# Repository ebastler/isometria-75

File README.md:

# isometria<sup>75</sup>

The first prototype is sitting on my desk and works perfectly - clearance for weights and battery is currently wrong, so the intended battery will not fit in the case.

----
 
 The name isometria<sup>75</sup> has it's origin in the greek noun ἰσομετρία (in latin letters: isometria), meaning "equality of measure" [[1]](http://perseus.uchicago.edu/cgi-bin/philologic/getobject.pl?c.35:6:59.LSJ). This word ended up being included in various languages, among them english (isometric), with the same meaning. I chose it for two reasons - because this keyboard is only available in an ISO layout (sorry ANSI users - for once it is ne ANSI avail), but also, because I paid attention to only use u/4 spaces throughout my board. You will have a hard time finding any distance on it that's not a multiple of 4.75 mm.

|||
|:----------------------------------------:|:----------------------------------------:|
|||
|||

 ## Features
 * CNC'd top shell with integrated 3 mm plate (obviously, with cutouts for switch retention and PCB mount stabs)
 * 6.8° typing angle
 * The PCB is equipped to fit 82 cherry MX-style switches
 * One 3 mm LED per switch (monochrome, dimmable only as one group)
 * 17 SK6812 Mini can be soldered to the bottom of the board for underglow
 * Fits either a battery-management or a simple USB-C daughterboard ([Repo link](https://github.com/ebastler/unified-usb-pcb))
 * A rotary encoder sits in the top right corner and the push-button is wired to the controller (Row 0 Column 15)
 * The USB-C connector is placed on a small PCB on it's own, which can be replaced by a battery management board
 * Sense wires to measure the input voltage and to check if the battery is currently being charged
 * A STM32F072CBT6 controller with native crystal-less USB and a lot of IO for various things
 * An SPI interface is wired to a second connector, allowing for a SPI Bluetooth LE board to be added
 * One leftover GPIO is available on a header - if you want to add something yourself

## Design
The PCB uses a key spacing of 19 mm (instead of the default 19.05), and all delimiters between key-blocks, or keys and the border of the case are 4.75 or 9.5 mm wide. This allows for a pleasantly homogenous design, which earned the keyboard it's name. Sadly, this layout requires a 1.5u right shift, which very few sets include. 

The bottom shell breaks the minimalist design of the top shell a little, with "stepped" faces. While the design originated from the need to make it easily millable on a 3 axis CNC, I appreciate the fact that it makes the board visually a bit more interesting.

## Geekhack project thread
https://geekhack.org/index.php?topic=106060.msg2896354

## FAQ:
 * Where can I buy this?

   I'm afraid there will not be any groupbuy nor will it be stocked at some reseller - All files are open source though, feel free to order a batch of PCBs and a case yourself - or improve it!

 * When will there be an ANSI version?

   Even though I planned not to do ANSI, I actually went with multi-layout for v2! Stay tuned!

 * Why did you clone the Evolv/Satisfaction?
 
   I made my own design choices, and designed everything from scratch - however the evolv heavily influenced my design. I fell in love with it the first time I saw it, but it had a few things I dislike. So I decided to mostly adopt it's layout with some changes, and design a case which follows my design ideals - ending up with a (visually) very similar top enclosure - The standalone-features of the evolv are it's premium materials, construction and generative design, and I did not include either.

For any other questions, or problems with my board (if you decided to build one yourself) - feel free to contact me. I'm idling around and occasionally check my PMs on freenode (ebastler), am active on reddit (the_ebastler) and on discord (ebastler#8966).

## Big thanks to:
 - ai03 for both his [great tutorial](https://wiki.ai03.me/books/pcb-design/chapter/pcb-designer-guide) as well as his various footprints I used in my design - I don't know if I had been able to design this without his help.
 - The awesome people on grabcad for the [MX switch](https://grabcad.com/library/cherry-mx-switches-mx-1), [Cherry Stab](https://grabcad.com/library/cherry-mx-stabilizer-mx-1) and [pushbutton](https://grabcad.com/library/5mm-button-switch-1) models, [JST SH models](https://grabcad.com/library/jst-sh-smd-connectors-1/details?folder_id=3903823) and [WS2812 Mini models](https://grabcad.com/library/smd-ws2812b-led-1) which made my design a whole lot easier, and my renders prettier.
  - People on the MechKeys and Mechanische Tastaturen Deutschland discord servers who tirelessly answered my questions - from the noobiest to the most complicated ones.
  - [Propagandalf1](https://github.com/Propagandalf1) for all the advise, criticism and ideas for improvement
  - Pseudoephedrin and Lux for checking my PCB layouts for errors
  - Hendrik for milling my proto

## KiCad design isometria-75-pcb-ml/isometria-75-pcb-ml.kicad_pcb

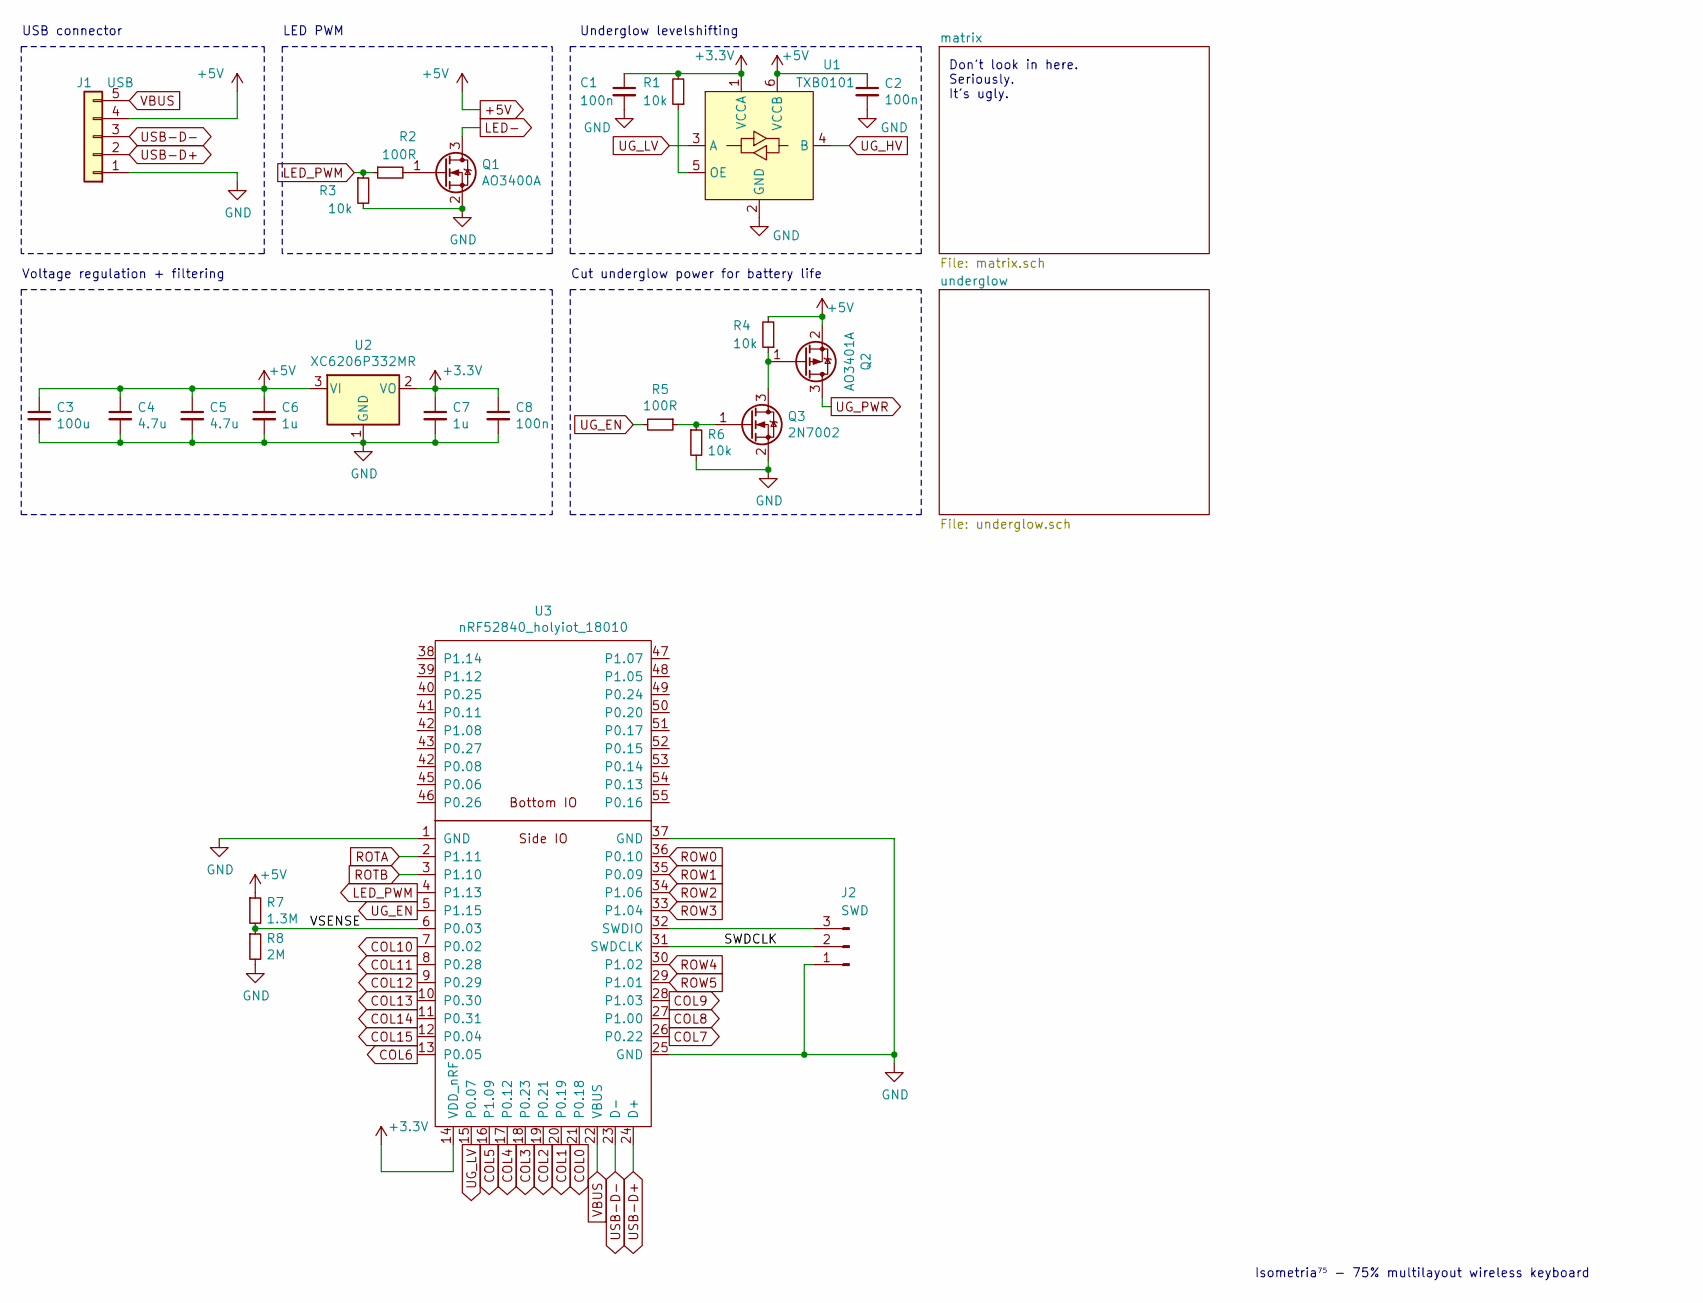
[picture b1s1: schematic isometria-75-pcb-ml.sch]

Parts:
C1, C2, C8: 100n; C_0603_1608Metric_Pad1.05x0.95mm_HandSolder; LCSC C386152
C3: 100u; CP_EIA-3528-21_Kemet-B; LCSC C16133
C4, C5: 4.7u; C_0603_1608Metric_Pad1.05x0.95mm_HandSolder; LCSC C1705
C6, C7: 1u; C_0603_1608Metric_Pad1.05x0.95mm_HandSolder; LCSC C15849
J1: USB; JST_SH_SM05B-SRSS-TB_1x05-1MP_P1.00mm_Horizontal; LCSC C136657
J2: SWD; PinHeader_1x03_P2.54mm_Vertical
Q1: AO3400A; SOT-23; LCSC C344010
Q2: AO3401A; SOT-23; LCSC C15127
Q3: 2N7002; SOT-23; LCSC C306856
R1, R3, R4, R6: 10k; R_0603_1608Metric_Pad1.05x0.95mm_HandSolder; LCSC C384294
R2, R5: 100R; R_0603_1608Metric_Pad1.05x0.95mm_HandSolder; LCSC C163844
R7: 1.3M; R_0603_1608Metric_Pad1.05x0.95mm_HandSolder; LCSC C170462
R8: 2M; R_0603_1608Metric_Pad1.05x0.95mm_HandSolder; LCSC C163894
U1: TXB0101; SOT-363_SC-70-6; LCSC C324081
U2: XC6206P332MR; SOT-23; LCSC C347376
U3: nRF52840_holyiot_18010

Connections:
+3V3: C1.1, C7.1, C8.1, R1.2, U1.1 (VCCA), U2.2 (VO), U3.14 (VDD_nRF); also elsewhere on the board
+5V: C2.1, C3.1, C4.1, C5.1, C6.1, J1.4, Q2.2 (S), R4.2, R7.1, U1.6 (VCCB), U2.3 (VI); also elsewhere on the board
/SWDCLK: J2.2, U3.31 (SWDCLK)
/VSENSE: R7.2, R8.1, U3.6 (P0.03)
COL0: U3.21 (P0.18); also elsewhere on the board
COL1: U3.20 (P0.19); also elsewhere on the board
COL2: U3.19 (P0.21); also elsewhere on the board
COL3: U3.18 (P0.23); also elsewhere on the board
COL4: U3.17 (P0.12); also elsewhere on the board
COL5: U3.16 (P1.09); also elsewhere on the board
COL6: U3.13 (P0.05); also elsewhere on the board
COL7: U3.26 (P0.22); also elsewhere on the board
COL8: U3.27 (P1.00); also elsewhere on the board
COL9: U3.28 (P1.03); also elsewhere on the board
COL10: U3.7 (P0.02); also elsewhere on the board
COL11: U3.8 (P0.28); also elsewhere on the board
COL12: U3.9 (P0.29); also elsewhere on the board
COL13: U3.10 (P0.30); also elsewhere on the board
COL14: U3.11 (P0.31); also elsewhere on the board
COL15: U3.12 (P0.04); also elsewhere on the board
GND: C1.2, C2.2, C3.2, C4.2, C5.2, C6.2, C7.2, C8.2, J1.1, J2.1, Q1.2 (S), Q3.2 (S), R3.2, R6.2, R8.2, U1.2 (GND), U2.1 (GND), U3.1 (GND), U3.25 (GND), U3.37 (GND); also elsewhere on the board
LED-: Q1.3 (D); also elsewhere on the board
LED_PWM: R2.1, R3.1, U3.4 (P1.13)
unnamed: J2.3, U3.32 (SWDIO)
unnamed: Q1.1 (G), R2.2
unnamed: Q2.1 (G), Q3.3 (D), R4.1
unnamed: Q3.1 (G), R5.1, R6.1
unnamed: R1.1, U1.5 (OE)
ROTA: U3.2 (P1.11); also elsewhere on the board
ROTB: U3.3 (P1.10); also elsewhere on the board
ROW0: U3.36 (P0.10); also elsewhere on the board
ROW1: U3.35 (P0.09); also elsewhere on the board
ROW2: U3.34 (P1.06); also elsewhere on the board
ROW3: U3.33 (P1.04); also elsewhere on the board
ROW4: U3.30 (P1.02); also elsewhere on the board
ROW5: U3.29 (P1.01); also elsewhere on the board
UG_EN: R5.2, U3.5 (P1.15)
UG_HV: U1.4 (B); also elsewhere on the board
UG_LV: U1.3 (A), U3.15 (P0.07)
UG_PWR: Q2.3 (D); also elsewhere on the board
USB-D+: J1.2, U3.24 (D+)
USB-D-: J1.3, U3.23 (D-)
VBUS: J1.5, U3.22 (VBUS)

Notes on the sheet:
USB connector
Voltage regulation + filtering
LED PWM
Don't look in here. Seriously. It's ugly.
Isometria⁷⁵ - 75% multilayout wireless keyboard
Underglow levelshifting
Cut underglow power for battery life

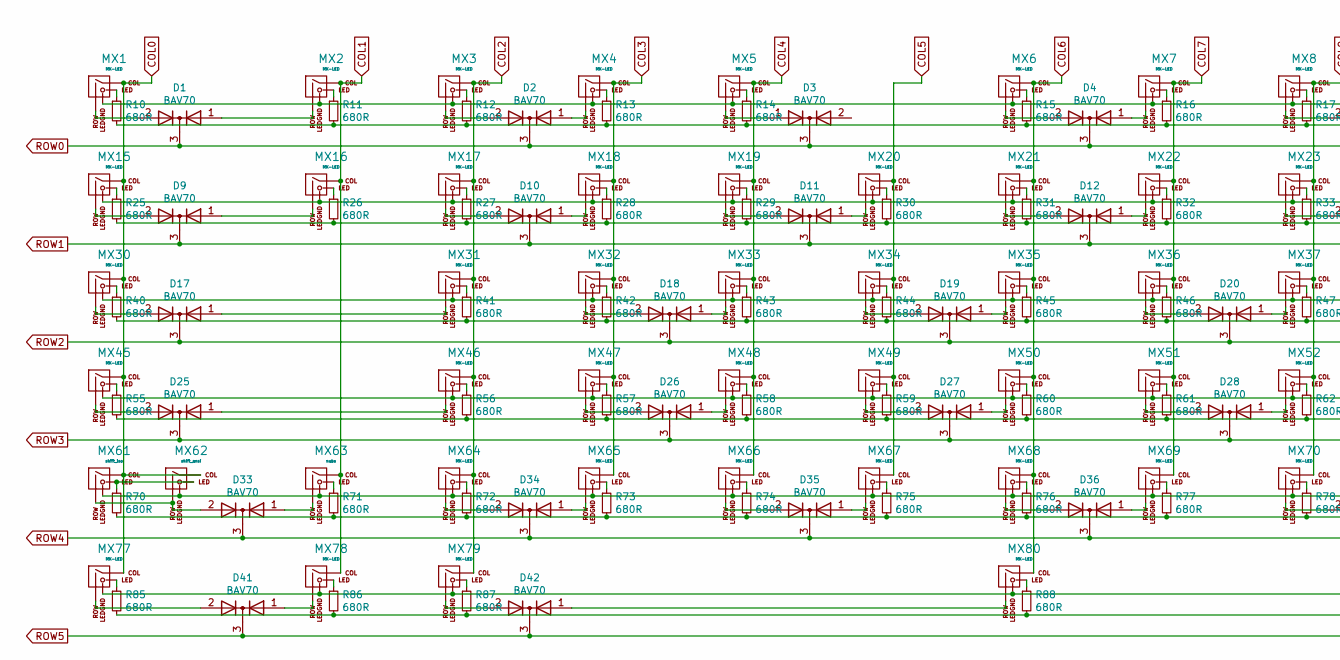
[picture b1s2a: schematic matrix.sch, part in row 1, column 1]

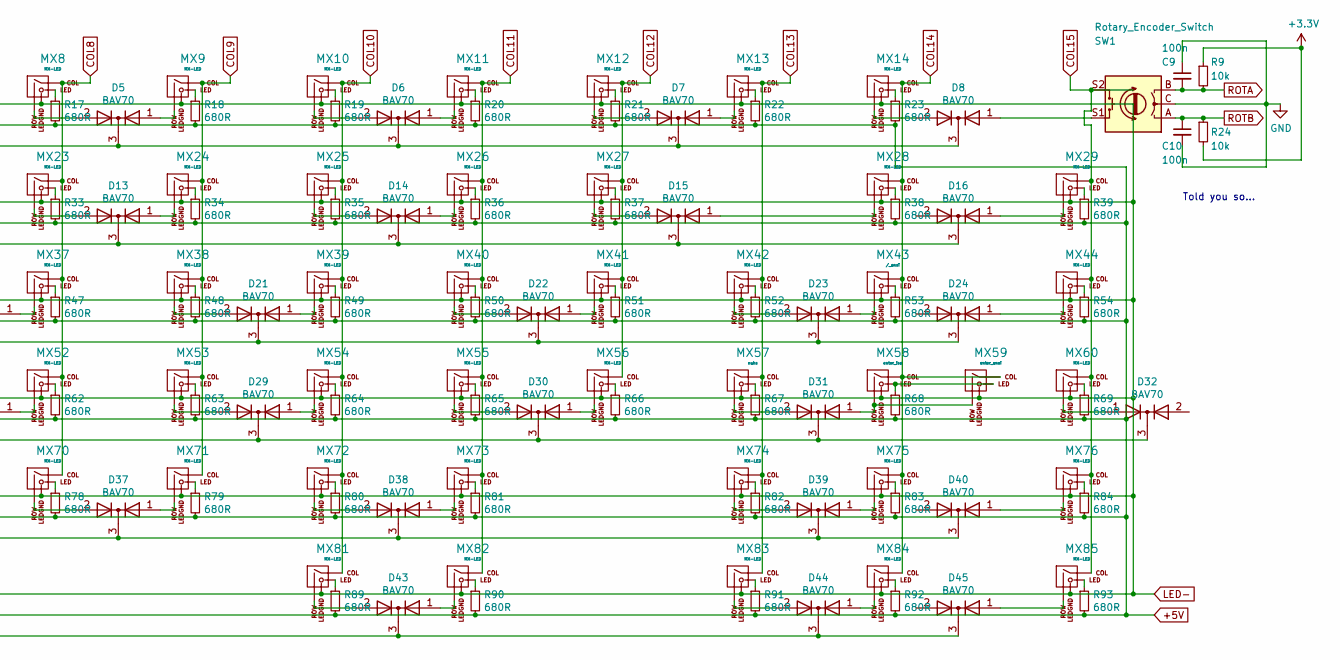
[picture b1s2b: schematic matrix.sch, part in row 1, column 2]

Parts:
C9, C10: 100n; C_0603_1608Metric_Pad1.05x0.95mm_HandSolder; LCSC C386152
D1, D2, D3, D4, D5, D6, D7, D8, D9, D10, D11, D12, D13, D14, D15, D16, D17, D18, D19, D20, D21, D22, D23, D24, D25, D26, D27, D28, D29, D30, D31, D32, D33, D34, D35, D36, D37, D38, D39, D40, D41, D42, D43, D44, D45: BAV70; SOT-23_stealth; LCSC C727123
MX1, MX2, MX3, MX4, MX5, MX6, MX7, MX8, MX9, MX10, MX11, MX12, MX13, MX14, MX15, MX16, MX17, MX18, MX19, MX20, MX21, MX22, MX23, MX24, MX25, MX26, MX27, MX29, MX31, MX32, MX33, MX34, MX35, MX36, MX37, MX38, MX39, MX40, MX41, MX42, MX44, MX46, MX47, MX48, MX49, MX50, MX51, MX52, MX53, MX54, MX55, MX56, MX60, MX64, MX65, MX66, MX67, MX68, MX69, MX70, MX71, MX72, MX73, MX75, MX76, MX83, MX84, MX85: MX-LED; MXOnly-1U
MX28: MX-LED; MXOnly-2U-ReversedStabilizers
MX30, MX74, MX81: MX-LED; MXOnly-1.5U
MX43: /_ansi; MXOnly-1.5U
MX45: MX-LED; MXOnly-1.75U
MX57: nuhs; MXOnly-1U
MX58: enter_iso; MXOnly-ISO-ROTATED
MX59: enter_ansi; MXOnly-2.25U
MX61: shift_iso; MXOnly-1.25U
MX62: shift_ansi; MXOnly-2.25U
MX63: nubs; MXOnly-1U
MX77, MX78, MX79, MX82: MX-LED; MXOnly-1.25U
MX80: MX-LED; MXOnly-6.25U
R9, R24: 10k; R_0603_1608Metric_Pad1.05x0.95mm_HandSolder; LCSC C384294
R10, R11, R12, R13, R14, R15, R16, R17, R18, R19, R20, R21, R22, R23, R25, R26, R27, R28, R29, R30, R31, R32, R33, R34, R35, R36, R37, R38, R39, R40, R41, R42, R43, R44, R45, R46, R47, R48, R49, R50, R51, R52, R53, R54, R55, R56, R57, R58, R59, R60, R61, R62, R63, R64, R65, R66, R67, R68, R69, R70, R71, R72, R73, R74, R75, R76, R77, R78, R79, R80, R81, R82, R83, R84, R85, R86, R87, R88, R89, R90, R91, R92, R93: 680R; R_0603_1608Metric_stealth_HandSolder; LCSC C23228
SW1: Rotary_Encoder_Switch; RotaryEncoder_Alps_EC11E-Switch_Vertical_H20mm

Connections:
+3V3: R9.1, R24.2; also elsewhere on the board
+5V: R10.2, R11.2, R12.2, R13.2, R14.2, R15.2, R16.2, R17.2, R18.2, R19.2, R20.2, R21.2, R22.2, R23.2, R25.2, R26.2, R27.2, R28.2, R29.2, R30.2, R31.2, R32.2, R33.2, R34.2, R35.2, R36.2, R37.2, R38.2, R39.2, R40.2, R41.2, R42.2, R43.2, R44.2, R45.2, R46.2, R47.2, R48.2, R49.2, R50.2, R51.2, R52.2, R53.2, R54.2, R55.2, R56.2, R57.2, R58.2, R59.2, R60.2, R61.2, R62.2, R63.2, R64.2, R65.2, R66.2, R67.2, R68.2, R69.2, R70.2, R71.2, R72.2, R73.2, R74.2, R75.2, R76.2, R77.2, R78.2, R79.2, R80.2, R81.2, R82.2, R83.2, R84.2, R85.2, R86.2, R87.2, R88.2, R89.2, R90.2, R91.2, R92.2, R93.2; also elsewhere on the board
COL0: MX1.1 (COL), MX15.1 (COL), MX30.1 (COL), MX45.1 (COL), MX61.1 (COL), MX62.1 (COL), MX77.1 (COL); also elsewhere on the board
COL1: MX2.1 (COL), MX16.1 (COL), MX63.1 (COL), MX78.1 (COL); also elsewhere on the board
COL2: MX3.1 (COL), MX17.1 (COL), MX31.1 (COL), MX46.1 (COL), MX64.1 (COL), MX79.1 (COL); also elsewhere on the board
COL3: MX4.1 (COL), MX18.1 (COL), MX32.1 (COL), MX47.1 (COL), MX65.1 (COL); also elsewhere on the board
COL4: MX5.1 (COL), MX19.1 (COL), MX33.1 (COL), MX48.1 (COL), MX66.1 (COL); also elsewhere on the board
COL5: MX20.1 (COL), MX34.1 (COL), MX49.1 (COL), MX67.1 (COL); also elsewhere on the board
COL6: MX6.1 (COL), MX21.1 (COL), MX35.1 (COL), MX50.1 (COL), MX68.1 (COL), MX80.1 (COL); also elsewhere on the board
COL7: MX7.1 (COL), MX22.1 (COL), MX36.1 (COL), MX51.1 (COL), MX69.1 (COL); also elsewhere on the board
COL8: MX8.1 (COL), MX23.1 (COL), MX37.1 (COL), MX52.1 (COL), MX70.1 (COL); also elsewhere on the board
COL9: MX9.1 (COL), MX24.1 (COL), MX38.1 (COL), MX53.1 (COL), MX71.1 (COL); also elsewhere on the board
COL10: MX10.1 (COL), MX25.1 (COL), MX39.1 (COL), MX54.1 (COL), MX72.1 (COL), MX81.1 (COL); also elsewhere on the board
COL11: MX11.1 (COL), MX26.1 (COL), MX40.1 (COL), MX55.1 (COL), MX73.1 (COL), MX82.1 (COL); also elsewhere on the board
COL12: MX12.1 (COL), MX27.1 (COL), MX41.1 (COL), MX56.1 (COL); also elsewhere on the board
COL13: MX13.1 (COL), MX42.1 (COL), MX57.1 (COL), MX74.1 (COL), MX83.1 (COL); also elsewhere on the board
COL14: MX14.1 (COL), MX28.1 (COL), MX43.1 (COL), MX58.1 (COL), MX59.1 (COL), MX75.1 (COL), MX84.1 (COL); also elsewhere on the board
COL15: MX29.1 (COL), MX44.1 (COL), MX60.1 (COL), MX76.1 (COL), MX85.1 (COL), SW1.S2; also elsewhere on the board
GND: C9.1, C10.2, SW1.C; also elsewhere on the board
LED-: MX1.4 (LEDGND), MX2.4 (LEDGND), MX3.4 (LEDGND), MX4.4 (LEDGND), MX5.4 (LEDGND), MX6.4 (LEDGND), MX7.4 (LEDGND), MX8.4 (LEDGND), MX9.4 (LEDGND), MX10.4 (LEDGND), MX11.4 (LEDGND), MX12.4 (LEDGND), MX13.4 (LEDGND), MX14.4 (LEDGND), MX15.4 (LEDGND), MX16.4 (LEDGND), MX17.4 (LEDGND), MX18.4 (LEDGND), MX19.4 (LEDGND), MX20.4 (LEDGND), MX21.4 (LEDGND), MX22.4 (LEDGND), MX23.4 (LEDGND), MX24.4 (LEDGND), MX25.4 (LEDGND), MX26.4 (LEDGND), MX27.4 (LEDGND), MX28.4 (LEDGND), MX29.4 (LEDGND), MX30.4 (LEDGND), MX31.4 (LEDGND), MX32.4 (LEDGND), MX33.4 (LEDGND), MX34.4 (LEDGND), MX35.4 (LEDGND), MX36.4 (LEDGND), MX37.4 (LEDGND), MX38.4 (LEDGND), MX39.4 (LEDGND), MX40.4 (LEDGND), MX41.4 (LEDGND), MX42.4 (LEDGND), MX43.4 (LEDGND), MX44.4 (LEDGND), MX45.4 (LEDGND), MX46.4 (LEDGND), MX47.4 (LEDGND), MX48.4 (LEDGND), MX49.4 (LEDGND), MX50.4 (LEDGND), MX51.4 (LEDGND), MX52.4 (LEDGND), MX53.4 (LEDGND), MX54.4 (LEDGND), MX55.4 (LEDGND), MX56.4 (LEDGND), MX57.4 (LEDGND), MX58.4 (LEDGND), MX59.4 (LEDGND), MX60.4 (LEDGND), MX61.4 (LEDGND), MX62.4 (LEDGND), MX63.4 (LEDGND), MX64.4 (LEDGND), MX65.4 (LEDGND), MX66.4 (LEDGND), MX67.4 (LEDGND), MX68.4 (LEDGND), MX69.4 (LEDGND), MX70.4 (LEDGND), MX71.4 (LEDGND), MX72.4 (LEDGND), MX73.4 (LEDGND), MX74.4 (LEDGND), MX75.4 (LEDGND), MX76.4 (LEDGND), MX77.4 (LEDGND), MX78.4 (LEDGND), MX79.4 (LEDGND), MX80.4 (LEDGND), MX81.4 (LEDGND), MX82.4 (LEDGND), MX83.4 (LEDGND), MX84.4 (LEDGND), MX85.4 (LEDGND); also elsewhere on the board
unnamed: D1.1 (A), MX2.2 (ROW)
unnamed: D1.2 (A), MX1.2 (ROW)
unnamed: D2.1 (A), MX4.2 (ROW)
unnamed: D2.2 (A), MX3.2 (ROW)
unnamed: D3.1 (A), MX5.2 (ROW)
unnamed: D4.1 (A), MX7.2 (ROW)
unnamed: D4.2 (A), MX6.2 (ROW)
unnamed: D5.1 (A), MX9.2 (ROW)
unnamed: D5.2 (A), MX8.2 (ROW)
unnamed: D6.1 (A), MX11.2 (ROW)
unnamed: D6.2 (A), MX10.2 (ROW)
unnamed: D7.1 (A), MX13.2 (ROW)
unnamed: D7.2 (A), MX12.2 (ROW)
unnamed: D8.1 (A), SW1.S1
unnamed: D8.2 (A), MX14.2 (ROW)
unnamed: D9.1 (A), MX16.2 (ROW)
unnamed: D9.2 (A), MX15.2 (ROW)
unnamed: D10.1 (A), MX18.2 (ROW)
unnamed: D10.2 (A), MX17.2 (ROW)
unnamed: D11.1 (A), MX20.2 (ROW)
unnamed: D11.2 (A), MX19.2 (ROW)
unnamed: D12.1 (A), MX22.2 (ROW)
unnamed: D12.2 (A), MX21.2 (ROW)
unnamed: D13.1 (A), MX24.2 (ROW)
unnamed: D13.2 (A), MX23.2 (ROW)
unnamed: D14.1 (A), MX26.2 (ROW)
unnamed: D14.2 (A), MX25.2 (ROW)
unnamed: D15.1 (A), MX28.2 (ROW)
unnamed: D15.2 (A), MX27.2 (ROW)
unnamed: D16.1 (A), MX29.2 (ROW)
unnamed: D17.1 (A), MX31.2 (ROW)
unnamed: D17.2 (A), MX30.2 (ROW)
unnamed: D18.1 (A), MX33.2 (ROW)
unnamed: D18.2 (A), MX32.2 (ROW)
unnamed: D19.1 (A), MX35.2 (ROW)
unnamed: D19.2 (A), MX34.2 (ROW)
unnamed: D20.1 (A), MX37.2 (ROW)
unnamed: D20.2 (A), MX36.2 (ROW)
unnamed: D21.1 (A), MX39.2 (ROW)
unnamed: D21.2 (A), MX38.2 (ROW)
unnamed: D22.1 (A), MX41.2 (ROW)
unnamed: D22.2 (A), MX40.2 (ROW)
unnamed: D23.1 (A), MX43.2 (ROW)
unnamed: D23.2 (A), MX42.2 (ROW)
unnamed: D24.1 (A), MX44.2 (ROW)
unnamed: D25.1 (A), MX46.2 (ROW)
unnamed: D25.2 (A), MX45.2 (ROW)
unnamed: D26.1 (A), MX48.2 (ROW)
unnamed: D26.2 (A), MX47.2 (ROW)
unnamed: D27.1 (A), MX50.2 (ROW)
unnamed: D27.2 (A), MX49.2 (ROW)
unnamed: D28.1 (A), MX52.2 (ROW)
unnamed: D28.2 (A), MX51.2 (ROW)
unnamed: D29.1 (A), MX54.2 (ROW)
unnamed: D29.2 (A), MX53.2 (ROW)
unnamed: D30.1 (A), MX56.2 (ROW)
unnamed: D30.2 (A), MX55.2 (ROW)
unnamed: D31.1 (A), MX58.2 (ROW), MX59.2 (ROW)
unnamed: D31.2 (A), MX57.2 (ROW)
unnamed: D32.1 (A), MX60.2 (ROW)
unnamed: D33.1 (A), MX63.2 (ROW)
unnamed: D33.2 (A), MX61.2 (ROW), MX62.2 (ROW)
unnamed: D34.1 (A), MX65.2 (ROW)
unnamed: D34.2 (A), MX64.2 (ROW)
unnamed: D35.1 (A), MX67.2 (ROW)
unnamed: D35.2 (A), MX66.2 (ROW)
unnamed: D36.1 (A), MX69.2 (ROW)
unnamed: D36.2 (A), MX68.2 (ROW)
unnamed: D37.1 (A), MX71.2 (ROW)
unnamed: D37.2 (A), MX70.2 (ROW)
unnamed: D38.1 (A), MX73.2 (ROW)
unnamed: D38.2 (A), MX72.2 (ROW)
unnamed: D39.1 (A), MX75.2 (ROW)
unnamed: D39.2 (A), MX74.2 (ROW)
unnamed: D40.1 (A), MX76.2 (ROW)
unnamed: D41.1 (A), MX78.2 (ROW)
unnamed: D41.2 (A), MX77.2 (ROW)
unnamed: D42.1 (A), MX80.2 (ROW)
unnamed: D42.2 (A), MX79.2 (ROW)
unnamed: D43.1 (A), MX82.2 (ROW)
unnamed: D43.2 (A), MX81.2 (ROW)
unnamed: D44.1 (A), MX84.2 (ROW)
unnamed: D44.2 (A), MX83.2 (ROW)
unnamed: D45.1 (A), MX85.2 (ROW)
unnamed: MX1.3 (LED), R10.1
unnamed: MX2.3 (LED), R11.1
unnamed: MX3.3 (LED), R12.1
unnamed: MX4.3 (LED), R13.1
unnamed: MX5.3 (LED), R14.1
unnamed: MX6.3 (LED), R15.1
unnamed: MX7.3 (LED), R16.1
unnamed: MX8.3 (LED), R17.1
unnamed: MX9.3 (LED), R18.1
unnamed: MX10.3 (LED), R19.1
unnamed: MX11.3 (LED), R20.1
unnamed: MX12.3 (LED), R21.1
unnamed: MX13.3 (LED), R22.1
unnamed: MX14.3 (LED), R23.1
unnamed: MX15.3 (LED), R25.1
unnamed: MX16.3 (LED), R26.1
unnamed: MX17.3 (LED), R27.1
unnamed: MX18.3 (LED), R28.1
unnamed: MX19.3 (LED), R29.1
unnamed: MX20.3 (LED), R30.1
unnamed: MX21.3 (LED), R31.1
unnamed: MX22.3 (LED), R32.1
unnamed: MX23.3 (LED), R33.1
unnamed: MX24.3 (LED), R34.1
unnamed: MX25.3 (LED), R35.1
unnamed: MX26.3 (LED), R36.1
unnamed: MX27.3 (LED), R37.1
unnamed: MX28.3 (LED), R38.1
unnamed: MX29.3 (LED), R39.1
unnamed: MX30.3 (LED), R40.1
unnamed: MX31.3 (LED), R41.1
unnamed: MX32.3 (LED), R42.1
unnamed: MX33.3 (LED), R43.1
unnamed: MX34.3 (LED), R44.1
unnamed: MX35.3 (LED), R45.1
unnamed: MX36.3 (LED), R46.1
unnamed: MX37.3 (LED), R47.1
unnamed: MX38.3 (LED), R48.1
unnamed: MX39.3 (LED), R49.1
unnamed: MX40.3 (LED), R50.1
unnamed: MX41.3 (LED), R51.1
unnamed: MX42.3 (LED), R52.1
unnamed: MX43.3 (LED), R53.1
unnamed: MX44.3 (LED), R54.1
unnamed: MX45.3 (LED), R55.1
unnamed: MX46.3 (LED), R56.1
unnamed: MX47.3 (LED), R57.1
unnamed: MX48.3 (LED), R58.1
unnamed: MX49.3 (LED), R59.1
unnamed: MX50.3 (LED), R60.1
unnamed: MX51.3 (LED), R61.1
unnamed: MX52.3 (LED), R62.1
unnamed: MX53.3 (LED), R63.1
unnamed: MX54.3 (LED), R64.1
unnamed: MX55.3 (LED), R65.1
unnamed: MX56.3 (LED), R66.1
unnamed: MX57.3 (LED), R67.1
unnamed: MX58.3 (LED), MX59.3 (LED), R68.1
unnamed: MX60.3 (LED), R69.1
unnamed: MX61.3 (LED), MX62.3 (LED), R70.1
unnamed: MX63.3 (LED), R71.1
unnamed: MX64.3 (LED), R72.1
unnamed: MX65.3 (LED), R73.1
unnamed: MX66.3 (LED), R74.1
unnamed: MX67.3 (LED), R75.1
unnamed: MX68.3 (LED), R76.1
unnamed: MX69.3 (LED), R77.1
unnamed: MX70.3 (LED), R78.1
unnamed: MX71.3 (LED), R79.1
unnamed: MX72.3 (LED), R80.1
unnamed: MX73.3 (LED), R81.1
unnamed: MX74.3 (LED), R82.1
unnamed: MX75.3 (LED), R83.1
unnamed: MX76.3 (LED), R84.1
unnamed: MX77.3 (LED), R85.1
unnamed: MX78.3 (LED), R86.1
unnamed: MX79.3 (LED), R87.1
unnamed: MX80.3 (LED), R88.1
unnamed: MX81.3 (LED), R89.1
unnamed: MX82.3 (LED), R90.1
unnamed: MX83.3 (LED), R91.1
unnamed: MX84.3 (LED), R92.1
unnamed: MX85.3 (LED), R93.1
ROTA: C9.2, R9.2, SW1.B; also elsewhere on the board
ROTB: C10.1, R24.1, SW1.A; also elsewhere on the board
ROW0: D1.3 (K), D2.3 (K), D3.3 (K), D4.3 (K), D5.3 (K), D6.3 (K), D7.3 (K), D8.3 (K); also elsewhere on the board
ROW1: D9.3 (K), D10.3 (K), D11.3 (K), D12.3 (K), D13.3 (K), D14.3 (K), D15.3 (K), D16.3 (K); also elsewhere on the board
ROW2: D17.3 (K), D18.3 (K), D19.3 (K), D20.3 (K), D21.3 (K), D22.3 (K), D23.3 (K), D24.3 (K); also elsewhere on the board
ROW3: D25.3 (K), D26.3 (K), D27.3 (K), D28.3 (K), D29.3 (K), D30.3 (K), D31.3 (K), D32.3 (K); also elsewhere on the board
ROW4: D33.3 (K), D34.3 (K), D35.3 (K), D36.3 (K), D37.3 (K), D38.3 (K), D39.3 (K), D40.3 (K); also elsewhere on the board
ROW5: D41.3 (K), D42.3 (K), D43.3 (K), D44.3 (K), D45.3 (K); also elsewhere on the board

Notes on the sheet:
Told you so...

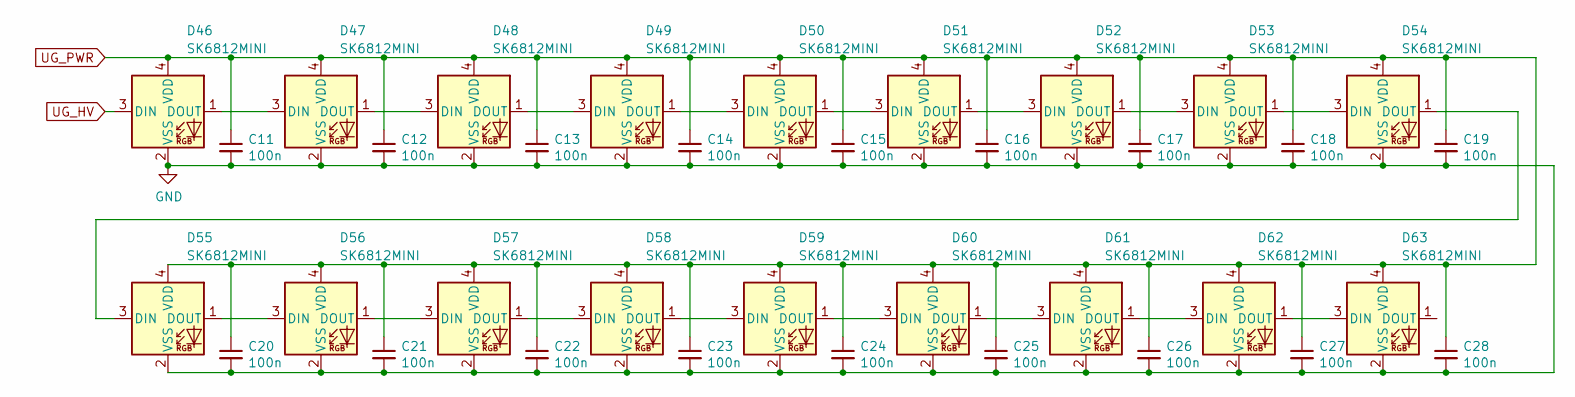
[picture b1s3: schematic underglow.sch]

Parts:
C11, C12, C13, C14, C15, C16, C17, C18, C19, C20, C21, C22, C23, C24, C25, C26, C27, C28: 100n; C_0603_1608Metric_Pad1.05x0.95mm_HandSolder; LCSC C386152
D46, D47, D48, D49, D50, D51, D52, D53, D54, D55, D56, D57, D58, D59, D60, D61, D62, D63: SK6812MINI; LED_SK6812MINI_PLCC4_3.5x3.5mm_P1.75mm

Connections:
GND: C11.2, C12.2, C13.2, C14.2, C15.2, C16.2, C17.2, C18.2, C19.2, C20.2, C21.2, C22.2, C23.2, C24.2, C25.2, C26.2, C27.2, C28.2, D46.2 (VSS), D47.2 (VSS), D48.2 (VSS), D49.2 (VSS), D50.2 (VSS), D51.2 (VSS), D52.2 (VSS), D53.2 (VSS), D54.2 (VSS), D55.2 (VSS), D56.2 (VSS), D57.2 (VSS), D58.2 (VSS), D59.2 (VSS), D60.2 (VSS), D61.2 (VSS), D62.2 (VSS), D63.2 (VSS); also elsewhere on the board
unnamed: D46.1 (DOUT), D47.3 (DIN)
unnamed: D47.1 (DOUT), D48.3 (DIN)
unnamed: D48.1 (DOUT), D49.3 (DIN)
unnamed: D49.1 (DOUT), D50.3 (DIN)
unnamed: D50.1 (DOUT), D51.3 (DIN)
unnamed: D51.1 (DOUT), D52.3 (DIN)
unnamed: D52.1 (DOUT), D53.3 (DIN)
unnamed: D53.1 (DOUT), D54.3 (DIN)
unnamed: D54.1 (DOUT), D55.3 (DIN)
unnamed: D55.1 (DOUT), D56.3 (DIN)
unnamed: D56.1 (DOUT), D57.3 (DIN)
unnamed: D57.1 (DOUT), D58.3 (DIN)
unnamed: D58.1 (DOUT), D59.3 (DIN)
unnamed: D59.1 (DOUT), D60.3 (DIN)
unnamed: D60.1 (DOUT), D61.3 (DIN)
unnamed: D61.1 (DOUT), D62.3 (DIN)
unnamed: D62.1 (DOUT), D63.3 (DIN)
UG_HV: D46.3 (DIN); also elsewhere on the board
UG_PWR: C11.1, C12.1, C13.1, C14.1, C15.1, C16.1, C17.1, C18.1, C19.1, C20.1, C21.1, C22.1, C23.1, C24.1, C25.1, C26.1, C27.1, C28.1, D46.4 (VDD), D47.4 (VDD), D48.4 (VDD), D49.4 (VDD), D50.4 (VDD), D51.4 (VDD), D52.4 (VDD), D53.4 (VDD), D54.4 (VDD), D55.4 (VDD), D56.4 (VDD), D57.4 (VDD), D58.4 (VDD), D59.4 (VDD), D60.4 (VDD), D61.4 (VDD), D62.4 (VDD), D63.4 (VDD); also elsewhere on the board

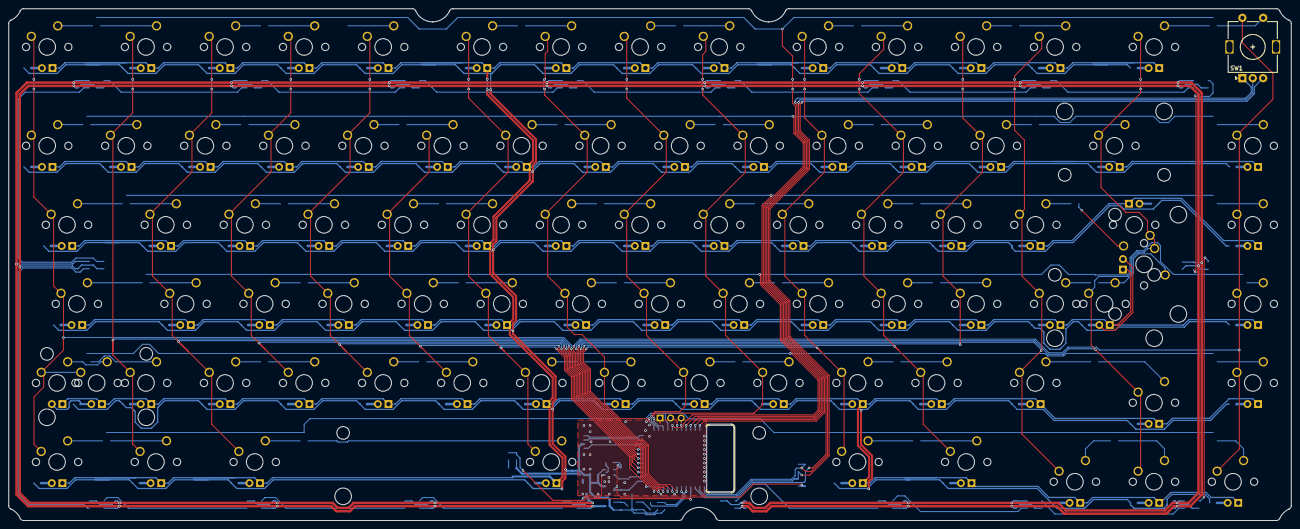
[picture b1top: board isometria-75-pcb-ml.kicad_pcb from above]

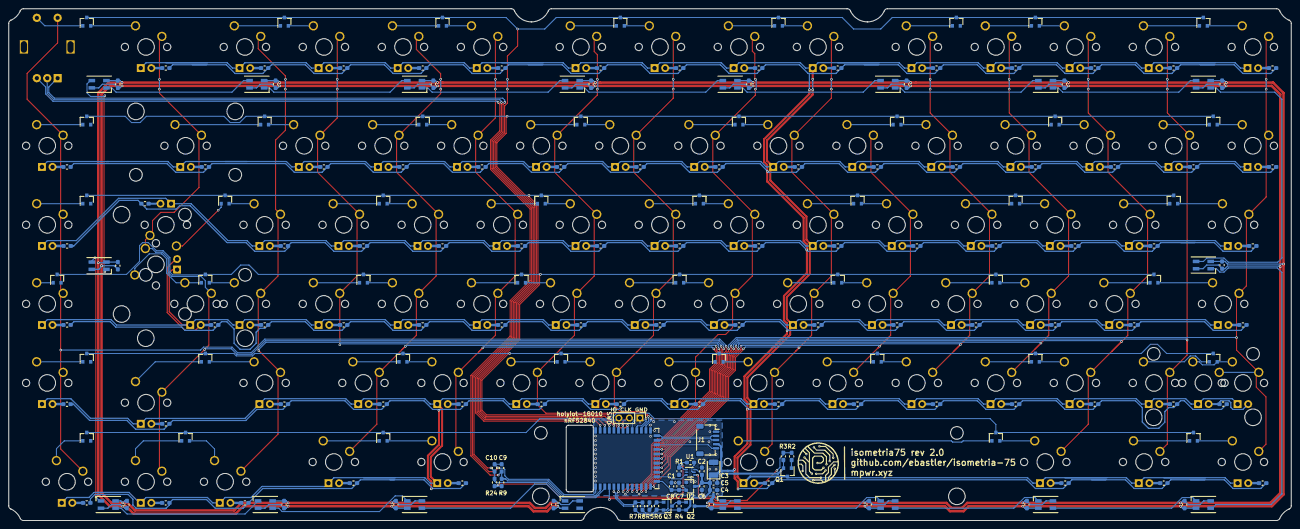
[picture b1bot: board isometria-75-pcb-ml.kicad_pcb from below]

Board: 2 copper layers, 308.3 x 123.0 mm, 278 parts (192 on the bottom side), 227 nets.
